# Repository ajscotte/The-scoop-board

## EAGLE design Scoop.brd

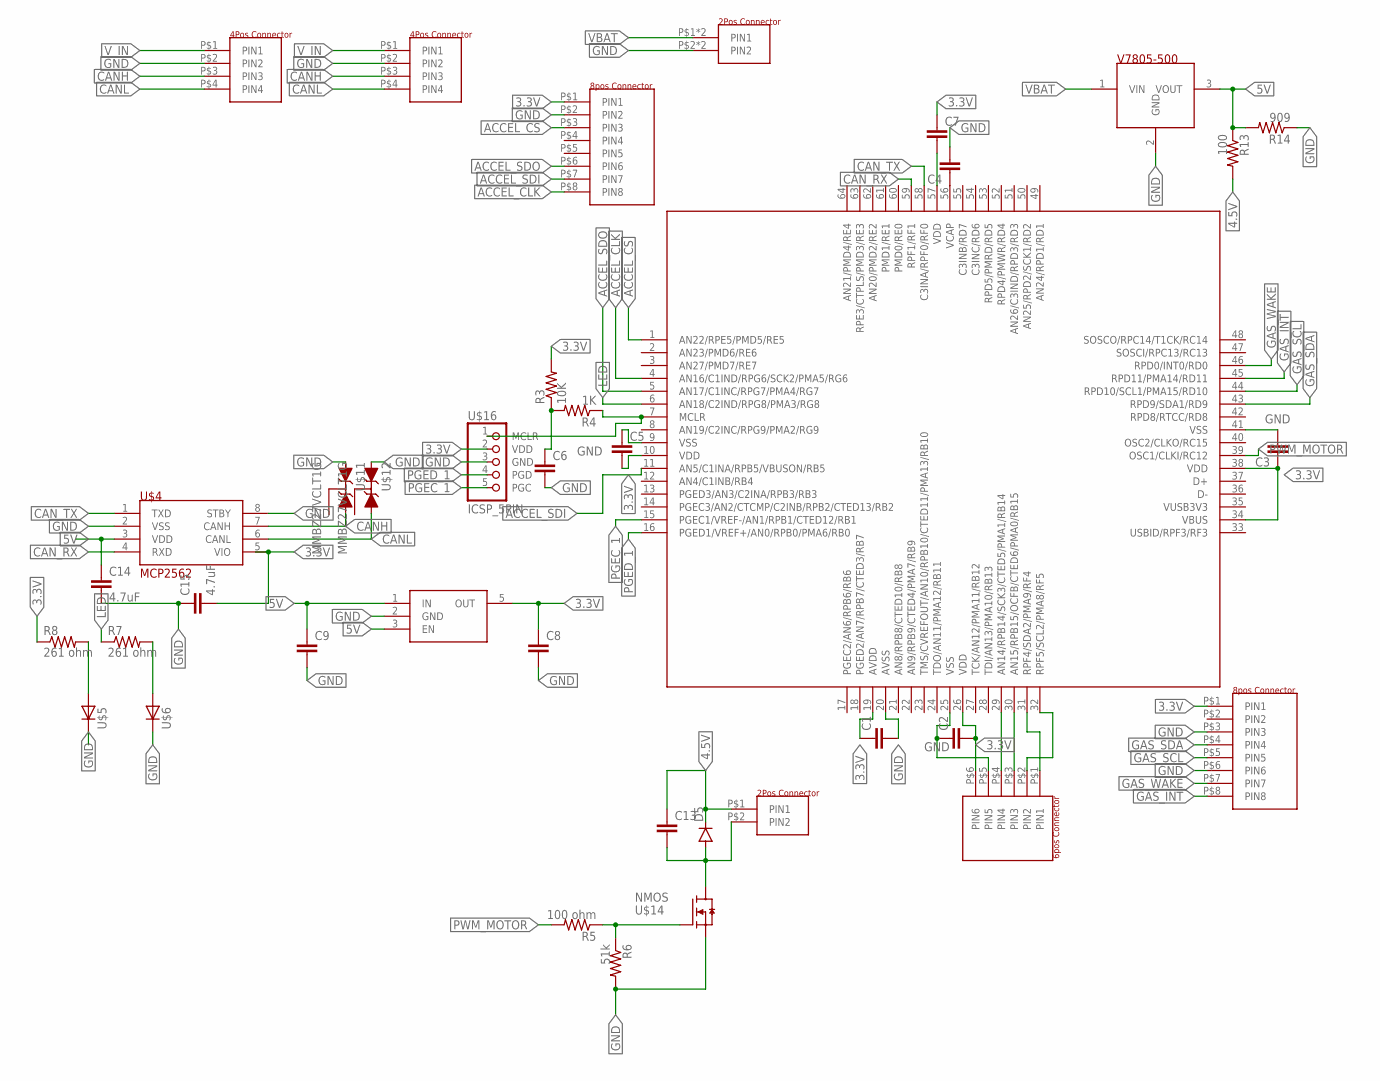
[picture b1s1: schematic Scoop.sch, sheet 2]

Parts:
C1, C2, C3, C5, C6, C7, C13: 0.1uF; 0603
C4: 10uF; 1206
C8, C9: 1uF; 0603
C14, C15: 4.7uF; 0603
D5: DIODE-SOD123; SOD123
R3: 10K; 0603
R4: 1K; 0603
R5: 100 ohm; 0603
R6: 51k; 0603
R7, R8: 261 ohm; 0603
R13: 100; 0603
R14: 909; 0603
U$1: PIC32MX530F128H"; QFP50P1200X1200X120-64
U$2: 2POS_CONNECTOR,1X2_45A_POWERPOLE; POWERPOLE_45A_1X2
U$4: MCP2562; SOIC8
U$5, U$6: LED0603; DO0603
U$7: 2POS_CONNECTOR,.1"HEADER; 2POS_HEADER_.1"
U$8: V7805-500; SIP3
U$9: TLV70233DBVR; SOT-23-5
U$10, U$15: 8POS_CONNECTOR; 8POS_XH_TOP
U$11, U$12: MMBZ27VCLT1G; SOT23
U$13: 6POS_CONNECTOR.1"PITCH_HEADERS; 6POS_HEADER_.1"
U$14: NMOS; SOT95P237X111-3N
U$16: ICSP_5PIN; ICSP_5
U$18, U$19: 4POS_CONNECTORMOLEX_MICROFIT3.0_RA_4PIN_2ROW; MOLEX_MICROFIT3.0_0430450400

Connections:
3.3V: C1.1, C2.2, C3.1, C5.2, C7.1, C8.1, C15.2, R3.2, R8.1, U$1.10 (VDD), U$1.19 (AVDD), U$1.26 (VDD), U$1.34 (VBUS), U$1.38 (VDD), U$4.5 (VIO), U$9.5 (OUT), U$10.P$1 (PIN1), U$13.P$6 (PIN6), U$15.P$1 (PIN1), U$16.2 (VDD)
4.5V: C13.1, D5.C, R13.2, U$7.P$1 (PIN1)
5V: C9.1, C14.1, R13.1, R14.2, U$4.3 (VDD), U$8.3 (VOUT), U$9.1 (IN), U$9.3 (EN)
ACCEL_CLK: U$1.4 (AN16/C1IND/RPG6/SCK2/PMA5/RG6), U$15.P$8 (PIN8)
ACCEL_CS: U$1.1 (AN22/RPE5/PMD5/RE5), U$15.P$3 (PIN3)
ACCEL_SDI: U$1.11 (AN5/C1INA/RPB5/VBUSON/RB5), U$15.P$7 (PIN7)
ACCEL_SDO: U$1.5 (AN17/C1INC/RPG7/PMA4/RG7), U$15.P$6 (PIN6)
CANH: U$4.7 (CANH), U$11.2 (A2), U$18.P$3 (PIN3), U$19.P$3 (PIN3)
CANL: U$4.6 (CANL), U$12.2 (A2), U$18.P$4 (PIN4), U$19.P$4 (PIN4)
CAN_RX: U$1.59 (RPF1/RF1), U$4.4 (RXD)
CAN_TX: U$1.58 (C3INA/RPF0/RF0), U$4.1 (TXD)
GAS_INT: U$1.45 (RPD11/PMA14/RD11), U$10.P$8 (PIN8)
GAS_SCL: U$1.44 (RPD10/SCL1/PMA15/RD10), U$10.P$5 (PIN5)
GAS_SDA: U$1.43 (RPD9/SDA1/RD9), U$10.P$4 (PIN4)
GAS_WAKE: U$1.46 (RPD0/INT0/RD0), U$10.P$7 (PIN7)
GND: C1.2, C2.1, C3.2, C4.2, C5.1, C6.2, C8.2, C9.2, C14.2, C15.1, R6.2, R14.1, U$1.9 (VSS), U$1.20 (AVSS), U$1.25 (VSS), U$1.41 (VSS), U$2.P$2 (PIN2), U$2.P$6 (PIN2), U$4.2 (VSS), U$4.8 (STBY), U$5.2 (C), U$6.2 (C), U$8.2 (GND), U$9.2 (GND), U$10.P$3 (PIN3), U$10.P$6 (PIN6), U$11.1 (A1), U$12.1 (A1), U$13.P$5 (PIN5), U$14.S, U$15.P$2 (PIN2), U$16.3 (GND), U$18.P$2 (PIN2), U$19.P$2 (PIN2)
LED: R7.1, U$1.6 (AN18/C2IND/RPG8/PMA3/RG8)
M2: C13.2, D5.A, U$7.P$2 (PIN2), U$14.D
unnamed: U$1.31 (RPF4/SDA2/PMA9/RF4), U$13.P$1 (PIN1)
unnamed: U$1.32 (RPF5/SCL2/PMA8/RF5), U$13.P$2 (PIN2)
unnamed: R7.2, U$6.1 (A)
unnamed: C6.1, R3.1, R4.2
unnamed: R5.1, R6.1, U$14.G
unnamed: R8.2, U$5.1 (A)
unnamed: C4.1, U$1.56 (VCAP)
unnamed: R4.1, U$1.7 (MCLR), U$16.1 (MCLR)
unnamed: U$1.30 (AN15/RPB15/OCFB/CTED6/PMA0/RB15), U$13.P$3 (PIN3)
unnamed: U$1.29 (AN14/RPB14/SCK3/CTED5/PMA1/RB14), U$13.P$4 (PIN4)
unnamed: C7.2, U$1.57 (VDD)
PGEC_1: U$1.15 (PGEC1/VREF-/AN1/RPB1/CTED12/RB1), U$16.5 (PGC)
PGED_1: U$1.16 (PGED1/VREF+/AN0/RPB0/PMA6/RB0), U$16.4 (PGD)
PWM_MOTOR: R5.2, U$1.39 (OSC1/CLKI/RC12)
VBAT: U$2.P$1 (PIN1), U$2.P$5 (PIN1), U$8.1 (VIN)
V_IN: U$18.P$1 (PIN1), U$19.P$1 (PIN1)

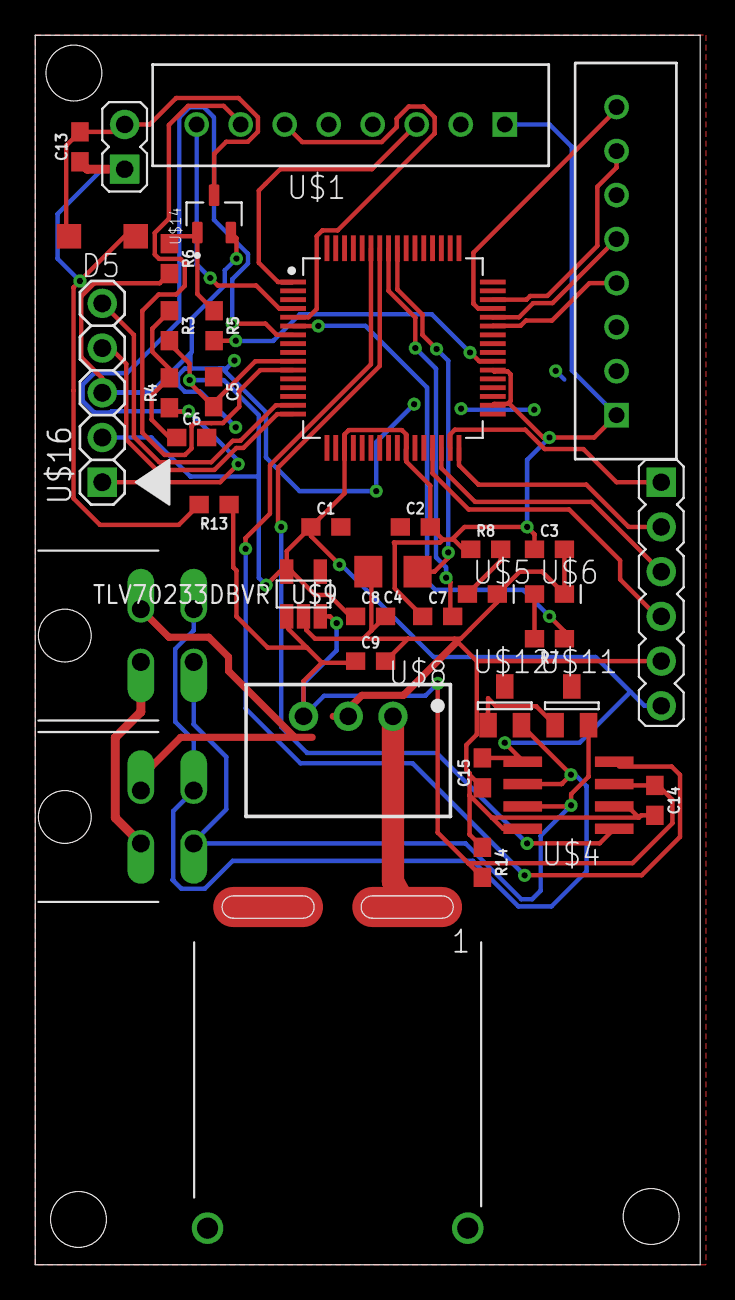
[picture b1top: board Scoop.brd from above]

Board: 2 copper layers, 37.8 x 69.8 mm, 38 parts (0 on the bottom side), 34 nets.

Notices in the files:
parts and their libraries:
SparkFun-Capacitors: Licensing: Creative Commons ShareAlike 4.0 International - https://creativecommons.org/licenses/by-sa/4.0
